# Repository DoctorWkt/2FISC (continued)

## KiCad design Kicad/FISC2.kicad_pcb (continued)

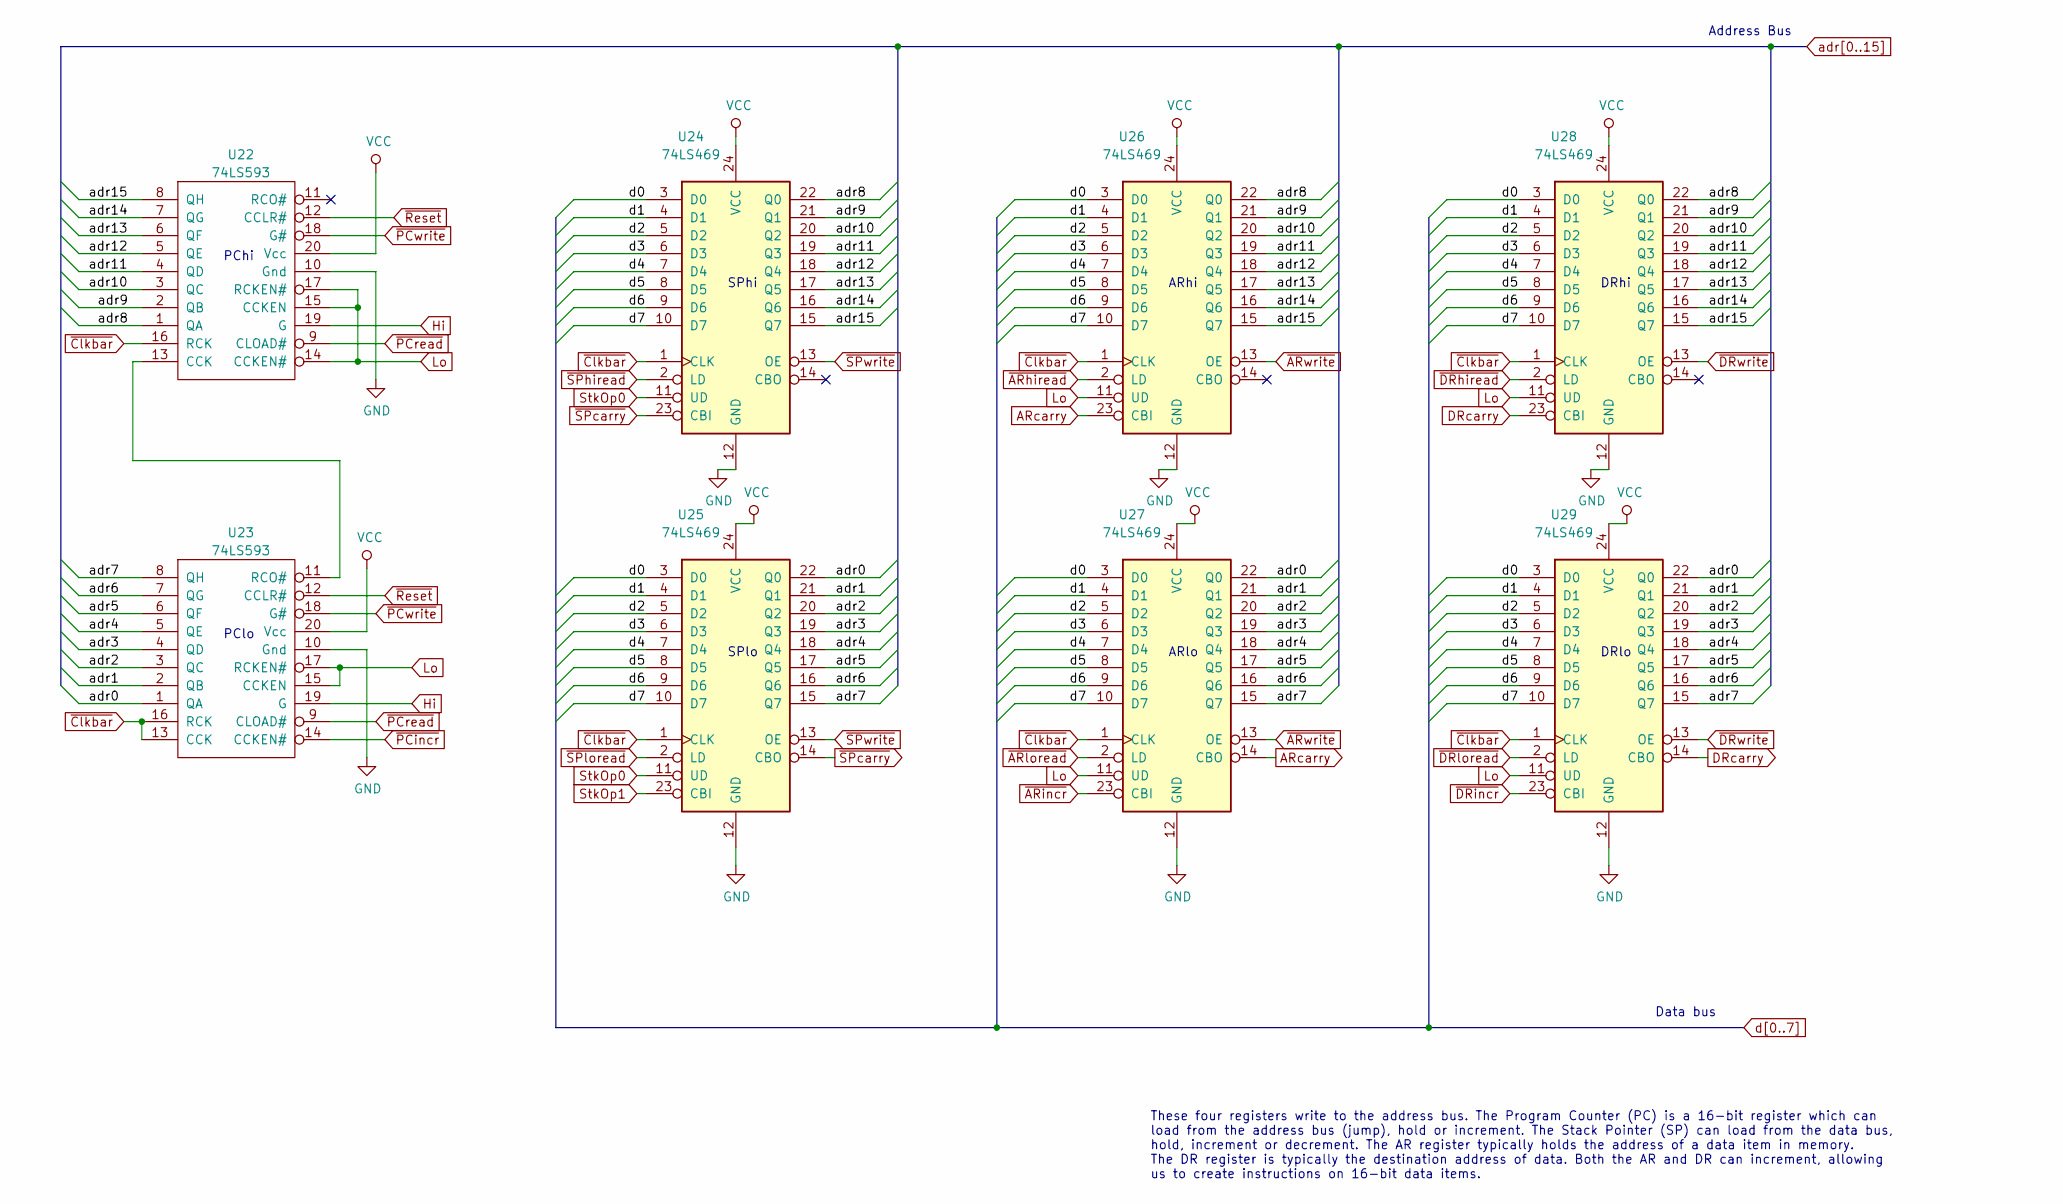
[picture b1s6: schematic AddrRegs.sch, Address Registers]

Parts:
U22, U23: 74LS593; SOIC-20W_7.5x12.8mm_P1.27mm
U24, U25, U26, U27, U28, U29: 74LS469; DIP-24_W7.62mm

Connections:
ARcarry: U26.23 (CBI), U27.14 (CBO)
DRcarry: U28.23 (CBI), U29.14 (CBO)
Hi: U22.19 (G), U22.20 (Vcc), U23.19 (G), U23.20 (Vcc), U24.24 (VCC), U25.24 (VCC), U26.24 (VCC), U27.24 (VCC), U28.24 (VCC), U29.24 (VCC); also elsewhere on the board
Lo: U22.10 (Gnd), U22.14 (CCKEN#), U22.15 (CCKEN), U22.17 (RCKEN#), U23.10 (Gnd), U23.15 (CCKEN), U23.17 (RCKEN#), U24.12 (GND), U25.12 (GND), U26.11 (UD), U26.12 (GND), U27.11 (UD), U27.12 (GND), U28.11 (UD), U28.12 (GND), U29.11 (UD), U29.12 (GND); also elsewhere on the board
NNNZout: U24.9 (D6), U25.9 (D6), U26.9 (D6), U27.9 (D6), U28.9 (D6), U29.9 (D6); also elsewhere on the board
unnamed: U22.13 (CCK), U23.11 (RCO#)
NorZout: U24.7 (D4), U25.7 (D4), U26.7 (D4), U27.7 (D4), U28.7 (D4), U29.7 (D4); also elsewhere on the board
NotZout: U24.6 (D3), U25.6 (D3), U26.6 (D3), U27.6 (D3), U28.6 (D3), U29.6 (D3); also elsewhere on the board
Nout: U24.5 (D2), U25.5 (D2), U26.5 (D2), U27.5 (D2), U28.5 (D2), U29.5 (D2); also elsewhere on the board
StkOp0: U24.11 (UD), U25.11 (UD); also elsewhere on the board
StkOp1: U25.23 (CBI); also elsewhere on the board
ZNNout: U24.8 (D5), U25.8 (D5), U26.8 (D5), U27.8 (D5), U28.8 (D5), U29.8 (D5); also elsewhere on the board
Zout: U24.4 (D1), U25.4 (D1), U26.4 (D1), U27.4 (D1), U28.4 (D1), U29.4 (D1); also elsewhere on the board
adr0: U23.1 (QA), U25.22 (Q0), U27.22 (Q0), U29.22 (Q0); also elsewhere on the board
adr1: U23.2 (QB), U25.21 (Q1), U27.21 (Q1), U29.21 (Q1); also elsewhere on the board
adr2: U23.3 (QC), U25.20 (Q2), U27.20 (Q2), U29.20 (Q2); also elsewhere on the board
adr3: U23.4 (QD), U25.19 (Q3), U27.19 (Q3), U29.19 (Q3); also elsewhere on the board
adr4: U23.5 (QE), U25.18 (Q4), U27.18 (Q4), U29.18 (Q4); also elsewhere on the board
adr5: U23.6 (QF), U25.17 (Q5), U27.17 (Q5), U29.17 (Q5); also elsewhere on the board
adr6: U23.7 (QG), U25.16 (Q6), U27.16 (Q6), U29.16 (Q6); also elsewhere on the board
adr7: U23.8 (QH), U25.15 (Q7), U27.15 (Q7), U29.15 (Q7); also elsewhere on the board
adr8: U22.1 (QA), U24.22 (Q0), U26.22 (Q0), U28.22 (Q0); also elsewhere on the board
adr9: U22.2 (QB), U24.21 (Q1), U26.21 (Q1), U28.21 (Q1); also elsewhere on the board
adr10: U22.3 (QC), U24.20 (Q2), U26.20 (Q2), U28.20 (Q2); also elsewhere on the board
adr11: U22.4 (QD), U24.19 (Q3), U26.19 (Q3), U28.19 (Q3); also elsewhere on the board
adr12: U22.5 (QE), U24.18 (Q4), U26.18 (Q4), U28.18 (Q4); also elsewhere on the board
adr13: U22.6 (QF), U24.17 (Q5), U26.17 (Q5), U28.17 (Q5); also elsewhere on the board
adr14: U22.7 (QG), U24.16 (Q6), U26.16 (Q6), U28.16 (Q6); also elsewhere on the board
adr15: U22.8 (QH), U24.15 (Q7), U26.15 (Q7), U28.15 (Q7); also elsewhere on the board
d0: U24.3 (D0), U25.3 (D0), U26.3 (D0), U27.3 (D0), U28.3 (D0), U29.3 (D0); also elsewhere on the board
d7: U24.10 (D7), U25.10 (D7), U26.10 (D7), U27.10 (D7), U28.10 (D7), U29.10 (D7); also elsewhere on the board
~ARhiread: U26.2 (LD); also elsewhere on the board
~ARincr: U27.23 (CBI); also elsewhere on the board
~ARloread: U27.2 (LD); also elsewhere on the board
~ARwrite: U26.13 (OE), U27.13 (OE); also elsewhere on the board
~Clkbar: U22.16 (RCK), U23.13 (CCK), U23.16 (RCK), U24.1 (CLK), U25.1 (CLK), U26.1 (CLK), U27.1 (CLK), U28.1 (CLK), U29.1 (CLK); also elsewhere on the board
~DRhiread: U28.2 (LD); also elsewhere on the board
~DRincr: U29.23 (CBI); also elsewhere on the board
~DRloread: U29.2 (LD); also elsewhere on the board
~DRwrite: U28.13 (OE), U29.13 (OE); also elsewhere on the board
~PCincr: U23.14 (CCKEN#); also elsewhere on the board
~PCread: U22.9 (CLOAD#), U23.9 (CLOAD#); also elsewhere on the board
~PCwrite: U22.18 (G#), U23.18 (G#); also elsewhere on the board
~Reset: U22.12 (CCLR#), U23.12 (CCLR#); also elsewhere on the board
~SPcarry: U24.23 (CBI), U25.14 (CBO)
~SPhiread: U24.2 (LD); also elsewhere on the board
~SPloread: U25.2 (LD); also elsewhere on the board
~SPwrite: U24.13 (OE), U25.13 (OE); also elsewhere on the board

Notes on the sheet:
SPhi
SPlo
PChi
PClo
Address Bus
ARhi
ARlo
DRhi
DRlo
Data bus
These four registers write to the address bus. The Program Counter (PC) is a 16-bit register which can load from the address bus (jump), hold or increment. The Stack Pointer (SP) can load from the data bus, hold, increment or decrement. The AR register typically holds the address of a data item in 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

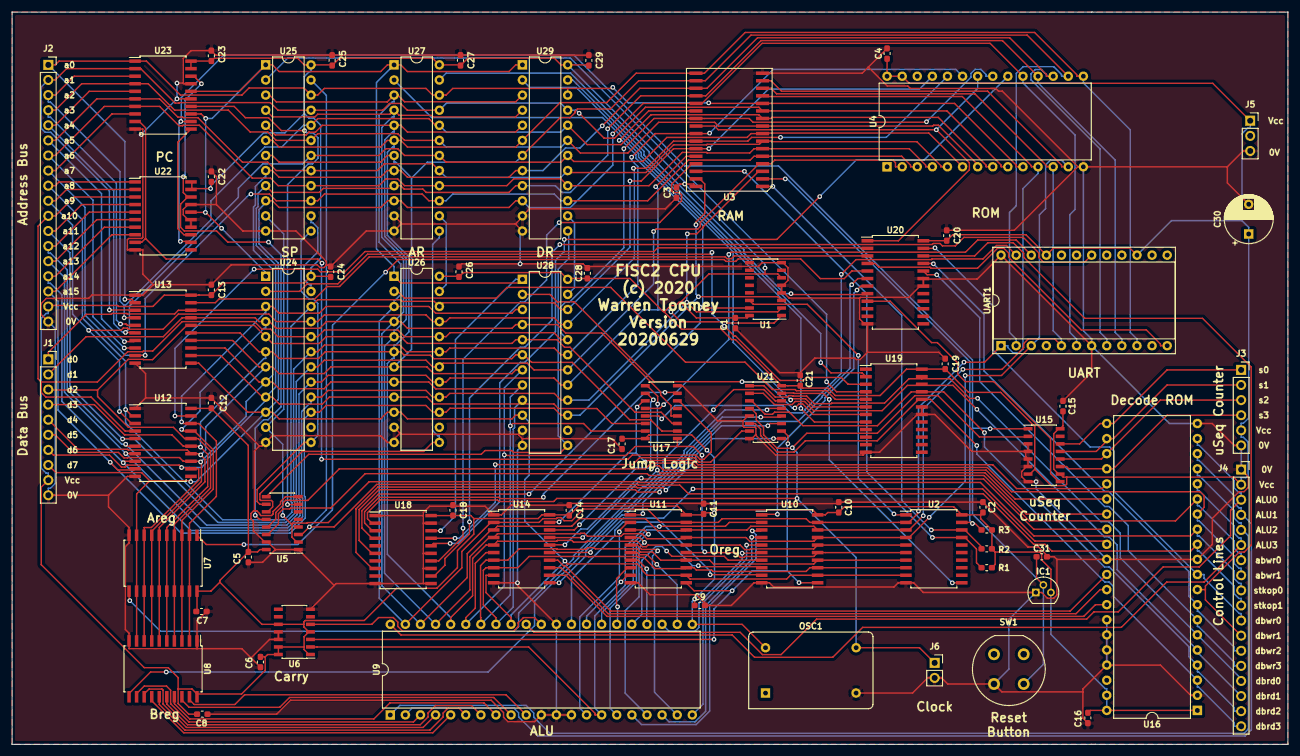
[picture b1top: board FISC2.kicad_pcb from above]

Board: 2 copper layers, 214.6 x 123.2 mm, 73 parts (0 on the bottom side), 127 nets.

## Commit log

2020-06-30 Initial commit to the GitHub repository.
2020-07-01 Added more journal, fixed typos.
2020-07-01 More journal entries.
2020-07-01 I updated some Verilog propagation delays
    based on my breadboard measurements.
2020-07-01 Updated schematic PDF, more journal entries.
2020-07-01 Taking on board feedback from Alan
2020-07-02 More journal entries: testing the 22K pullups.
2020-07-02 The PCB design is done, schematic updated, PCBs ordered.
2020-07-04 Some assembler improvements: names for X, Y and SP registers.
2020-07-05 Added a macro parser to gen_ucode.
    This should help to reduce the amount of DRY code
    in the microcode file.
2020-07-05 More microcode macros added.
2020-07-05 More instructions, mostly for local variables.
2020-07-06 Added .text and .data pseudo-ops to the assembler.
2020-07-06 I got a puts() working, finally.
2020-07-07 Added more instructions, assembler processes multiple files.
2020-07-08 Added numeric labels to the assembler. Renamed X, Y registers.
2020-07-11 Wrote a ROM monitor for the CPU.
2020-07-11 Fixed cas permission.
2020-07-11 Several changes.
    Brought clc up to date with the new instruction mnemonics.
    cas can now deal with negative stack offsets. Added one
    more instruction to the microcode.
2020-07-11 Microcode file can now have backslashes to join lines. csim now understands the new a.out format.
